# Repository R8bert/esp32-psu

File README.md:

# ⚡ ESP32-Controlled Lab Power Supply

A smart, programmable **lab power supply** controlled by an **ESP32 microcontroller**.  
This project combines hardware design and firmware development to provide precise, remote control over voltage and current using a **custom-designed PCB**.

---

## 🧠 Project Overview

This project was created to make a standard lab power supply smarter and easier to use.  
By adding an ESP32 and a custom interface board, I was able to control voltage, current, and safety features remotely — either through a web dashboard, serial commands, or a mobile app.

The repository includes both the **ESP32 firmware** and **PCB schematics** for full reproducibility.

---

## ⚙️ Features

- **Precise Voltage and Current Control**  
  Adjust and monitor power output in real time with fine-grained accuracy.

- **Multiple Control Interfaces**  
  Control the supply through a web interface, serial monitor, or a custom mobile app.

- **Programmable Output Profiles**  
  Automate experiments by predefining voltage/current sequences.

- **Built-in Safety Protections**  
  Includes software-based overvoltage and overcurrent protection to safeguard connected devices.

- **Custom PCB Design**  
  Handles signal conditioning and power control between the ESP32 and the lab power supply.

---

## 🧩 Components Used

| Component | Description |
|------------|-------------|
| **ESP32 DevKit** | Main controller, handles communication and web interface |
| **Custom PCB** | Connects ESP32 to lab supply, includes signal conditioning and protection |
| **Lab Power Supply** | Provides adjustable voltage and current output |
| **MOSFETs, Diodes, Resistors, Capacitors** | Used for power regulation and switching |
| **Connectors & Headers** | For input/output and debugging connections |

---

## 🔌 Schematics

The schematic below shows how the ESP32 interfaces with the lab power supply via the custom PCB.

---

## 💻 Firmware

The ESP32 firmware handles communication, user commands, and power control logic.

- Written in **C++** using the **Arduino framework**
- Communicates with the lab supply over digital I/O and serial protocols
- Supports **web-based control** via Wi-Fi and **serial communication**
- Implements **PID-style regulation** for smooth voltage and current control

### 🔧 Installation

1. Install the **Arduino IDE** or **PlatformIO** with ESP32 board support.  
2. Clone this repository.  
3. Open the firmware folder in your IDE.  
4. Compile and upload the code to the ESP32 board.  
5. Connect the ESP32 to the custom PCB and power supply.  

--
You can upload them directly to any PCB fabrication service (e.g., JLCPCB, PCBWay).

### 🔩 Assembly

Solder the through-hole and SMD components as labeled on the silkscreen.  
Pay attention to MOSFET orientation and connector alignment.

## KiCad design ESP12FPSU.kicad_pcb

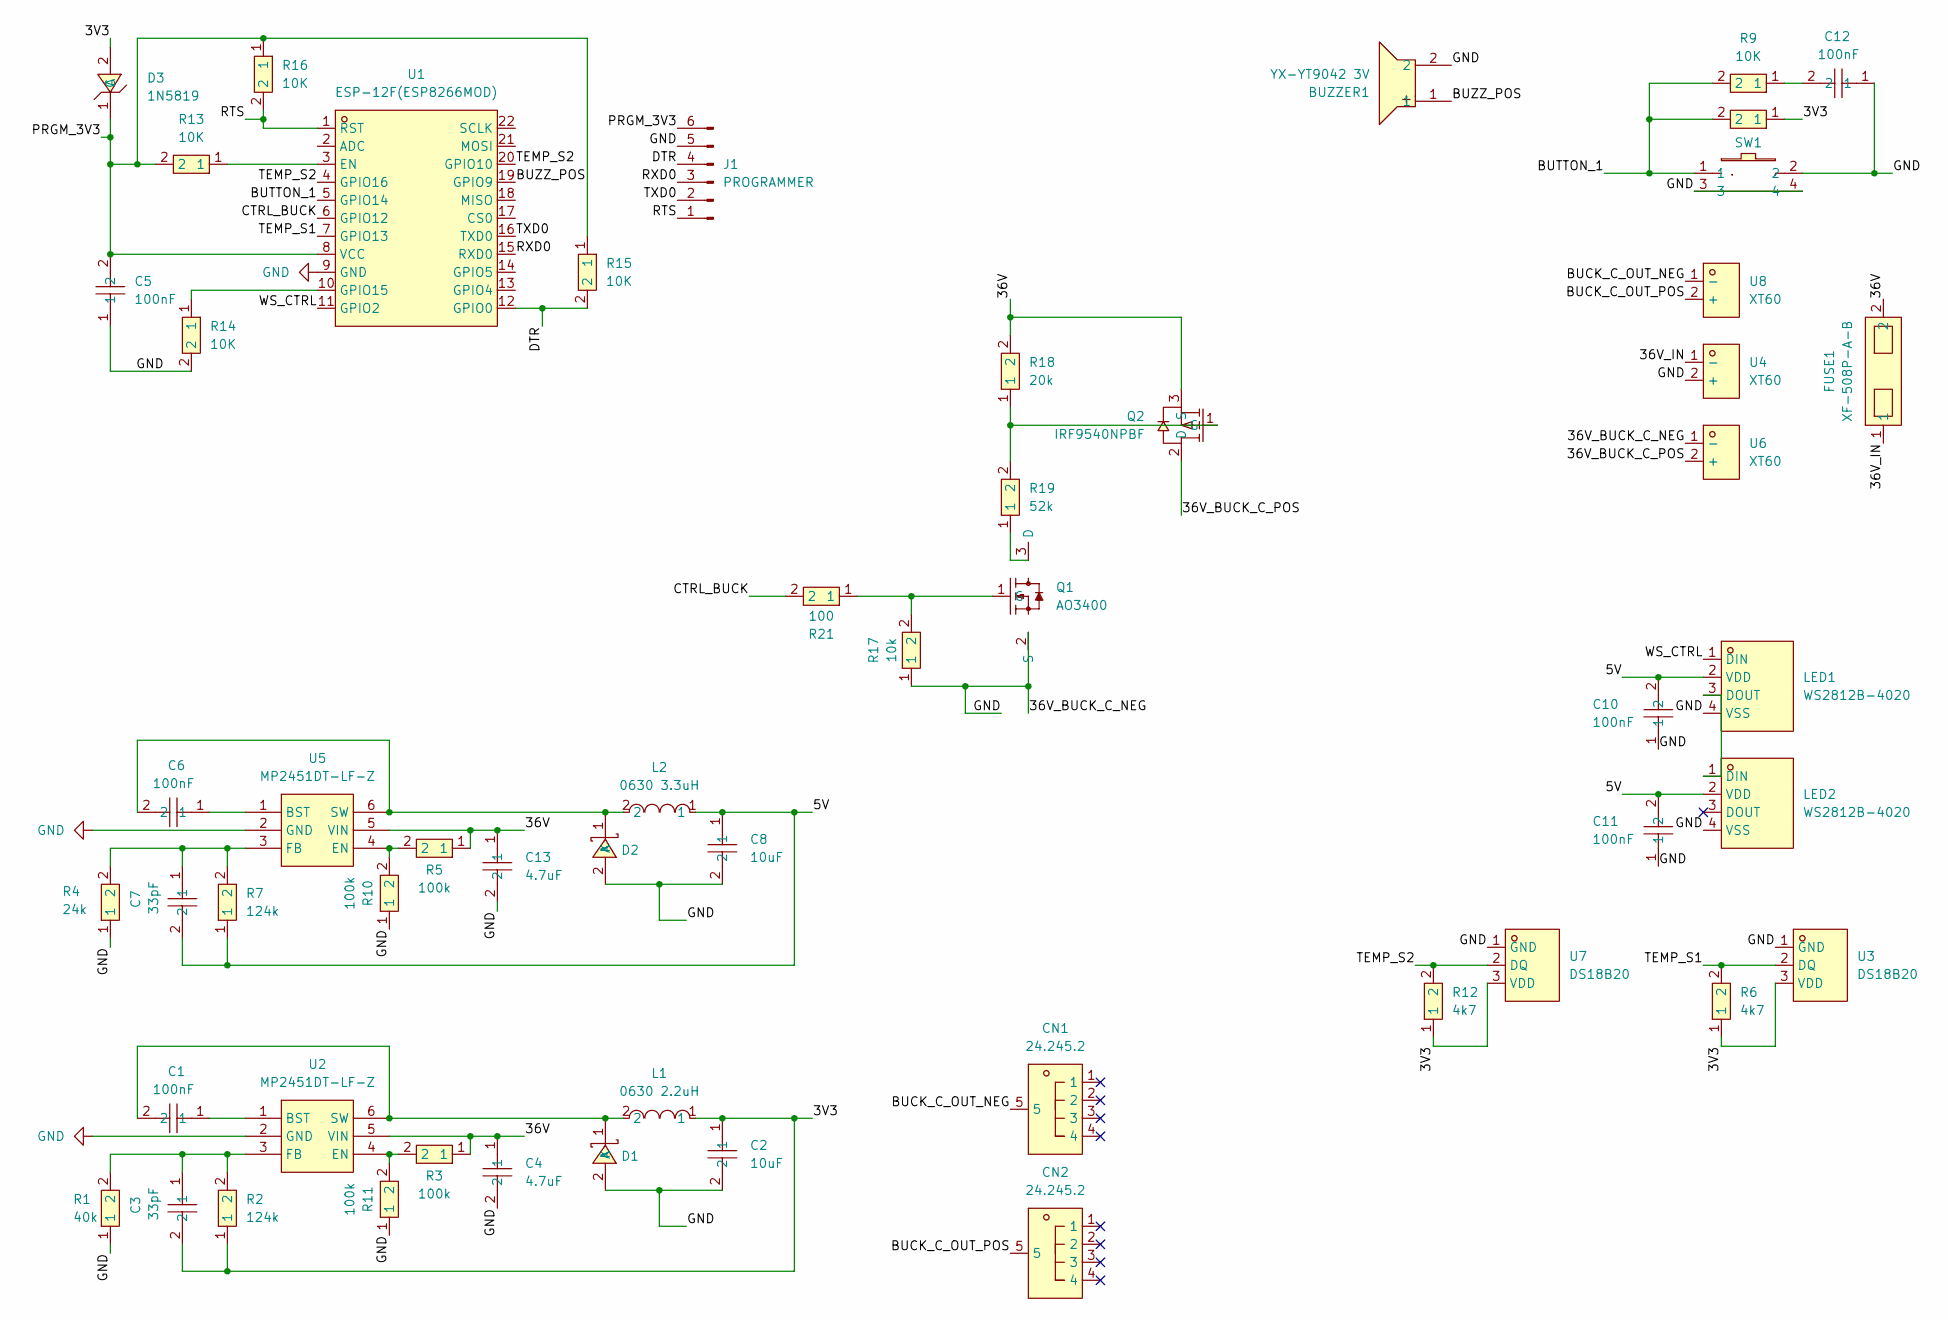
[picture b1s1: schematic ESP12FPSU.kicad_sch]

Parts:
BUZZER1: YX-YT9042 3V; BUZ-TH_BD9.0-P5.00-D0.6-FD; LCSC Part C781847
C1, C5, C6, C12: 100nF; C0603; LCSC Part C282519
C2, C8: 10uF; C1206; LCSC Part C105197
C3, C7: 33pF; C0603; LCSC Part C282519
C4, C13: 4.7uF; C1206; LCSC Part C105197
C10, C11: 100nF; C0603; LCSC Part C519946
CN1, CN2: 24.245.2; ANT-TH_L33.0-W12.0_BLACK; LCSC Part C7437327
D1, D2: SS24_C908678; SMA_L4.2-W2.7-LS5.1-RD; LCSC Part C908678
D3: 1N5819; SOD-123_L2.8-W1.8-LS3.7-RD; LCSC Part C402219
FUSE1: XF-508P-A-B; FUSE-TH_XF-508P-A-B; LCSC Part C19727304
J1: PROGRAMMER; PinHeader_1x06_P2.54mm_Vertical
L1: 0630 2.2uH; IND-SMD_L7.0-W6.6_0630CDMCCDS; LCSC Part C2961890
L2: 0630 3.3uH; IND-SMD_L7.0-W6.6_0630CDMCCDS; LCSC Part C2961890
LED1, LED2: WS2812B-4020; LED-SMD_WS2812B-4020; LCSC Part C965557
Q1: AO3400; SOT-23-3_L2.9-W1.3-P1.90-LS2.4-BR; LCSC Part C181090
Q2: IRF9540NPBF; TO-220-3_L10.0-W4.5-P2.54-L; LCSC Part C2575
R1: 40k; R0603; LCSC Part C2918515
R2, R7: 124k; R0603; LCSC Part C2918515
R3, R5, R10, R11: 100k; R0603; LCSC Part C2918515
R4: 24k; R0603; LCSC Part C2918515
R6, R12: 4k7; R0603; LCSC Part C2918515
R8, R9, R13, R14, R15, R16: 10K; R0603; LCSC Part C2918515
R17: 10k; R0603; LCSC Part C2918515
R18: 20k; R2512; LCSC Part C2889857
R19: 52k; R2512; LCSC Part C2889857
R21: 100; R0603; LCSC Part C2918515
SW1: Button-6x6x9-Right-Angle; SW-TH_BBJ; LCSC Part C71842
U1: ESP-12F(ESP8266MOD); WIFIM-SMD_ESP-12F-ESP8266MOD; LCSC Part C82891
U2, U5: MP2451DT-LF-Z; SOT-23-6_L2.9-W1.6-P0.95-LS2.8-BR; LCSC Part C14123
U3, U7: DS18B20; TO-92-3_L4.9-W3.7-P1.27-L; LCSC Part C376006
U4, U6, U8: XT60; CONN-TH_XT60; LCSC Part C98733

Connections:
/3V3: C2.1, C3.2, D3.2 (A), L1.1, R2.1, R6.1, R8.1, R12.1, U3.3 (VDD), U7.3 (VDD)
/5V: C7.2, C8.1, C10.2, C11.2, L2.1, LED1.2 (VDD), LED2.2 (VDD), R7.1
/36V: C4.1, C13.1, FUSE1.2, Q2.3 (S), R3.1, R5.1, R18.2, U2.5 (VIN), U5.5 (VIN)
/36V_BUCK_C_POS: Q2.2 (D), U6.2 (+)
/36V_IN: FUSE1.1, U4.1 (-)
/BUCK_C_OUT_NEG: CN1.5, U8.1 (-)
/BUCK_C_OUT_POS: CN2.5, U8.2 (+)
/BUTTON_1: R8.2, R9.2, SW1.1, U1.5 (GPIO14)
/BUZZ_POS: BUZZER1.1, U1.19 (GPIO9)
/CTRL_BUCK: R21.2, U1.6 (GPIO12)
/DTR: J1.4, R15.2, U1.12 (GPIO0)
/PRGM_3V3: C5.2, D3.1 (C), J1.6, R13.2, R15.1, R16.1, U1.8 (VCC)
/RTS: J1.1, R16.2, U1.1 (RST)
/RXD0: J1.3, U1.15 (RXD0)
/TEMP_S1: R6.2, U1.7 (GPIO13), U3.2 (DQ)
/TEMP_S2: R12.2, U1.4 (GPIO16), U1.20 (GPIO10), U7.2 (DQ)
/TXD0: J1.2, U1.16 (TXD0)
/WS_CTRL: LED1.1 (DIN), U1.11 (GPIO2)
GND: BUZZER1.2, C2.2, C4.2, C5.1, C8.2, C10.1, C11.1, C12.1, C13.2, D1.2 (A), D2.2 (A), J1.5, LED1.4 (VSS), LED2.4 (VSS), Q1.2 (S), R1.1, R4.1, R10.1, R11.1, R14.2, R17.1, SW1.2, SW1.3, SW1.4, U1.9 (GND), U2.2 (GND), U3.1 (GND), U4.2 (+), U5.2 (GND), U6.1 (-), U7.1 (GND)
unnamed: C12.2, R9.1
unnamed: C1.2, D1.1 (K), L1.2, U2.6 (SW)
unnamed: C6.2, D2.1 (K), L2.2, U5.6 (SW)
unnamed: LED1.3 (DOUT), LED2.1 (DIN)
unnamed: Q1.3 (D), R19.1
unnamed: Q1.1 (G), R17.2, R21.1
unnamed: Q2.1 (G), R18.1, R19.2
unnamed: R13.1, U1.3 (EN)
unnamed: R14.1, U1.10 (GPIO15)
unnamed: C1.1, U2.1 (BST)
unnamed: R3.2, R11.2, U2.4 (EN)
unnamed: C3.1, R1.2, R2.2, U2.3 (FB)
unnamed: C6.1, U5.1 (BST)
unnamed: R5.2, R10.2, U5.4 (EN)
unnamed: C7.1, R4.2, R7.2, U5.3 (FB)

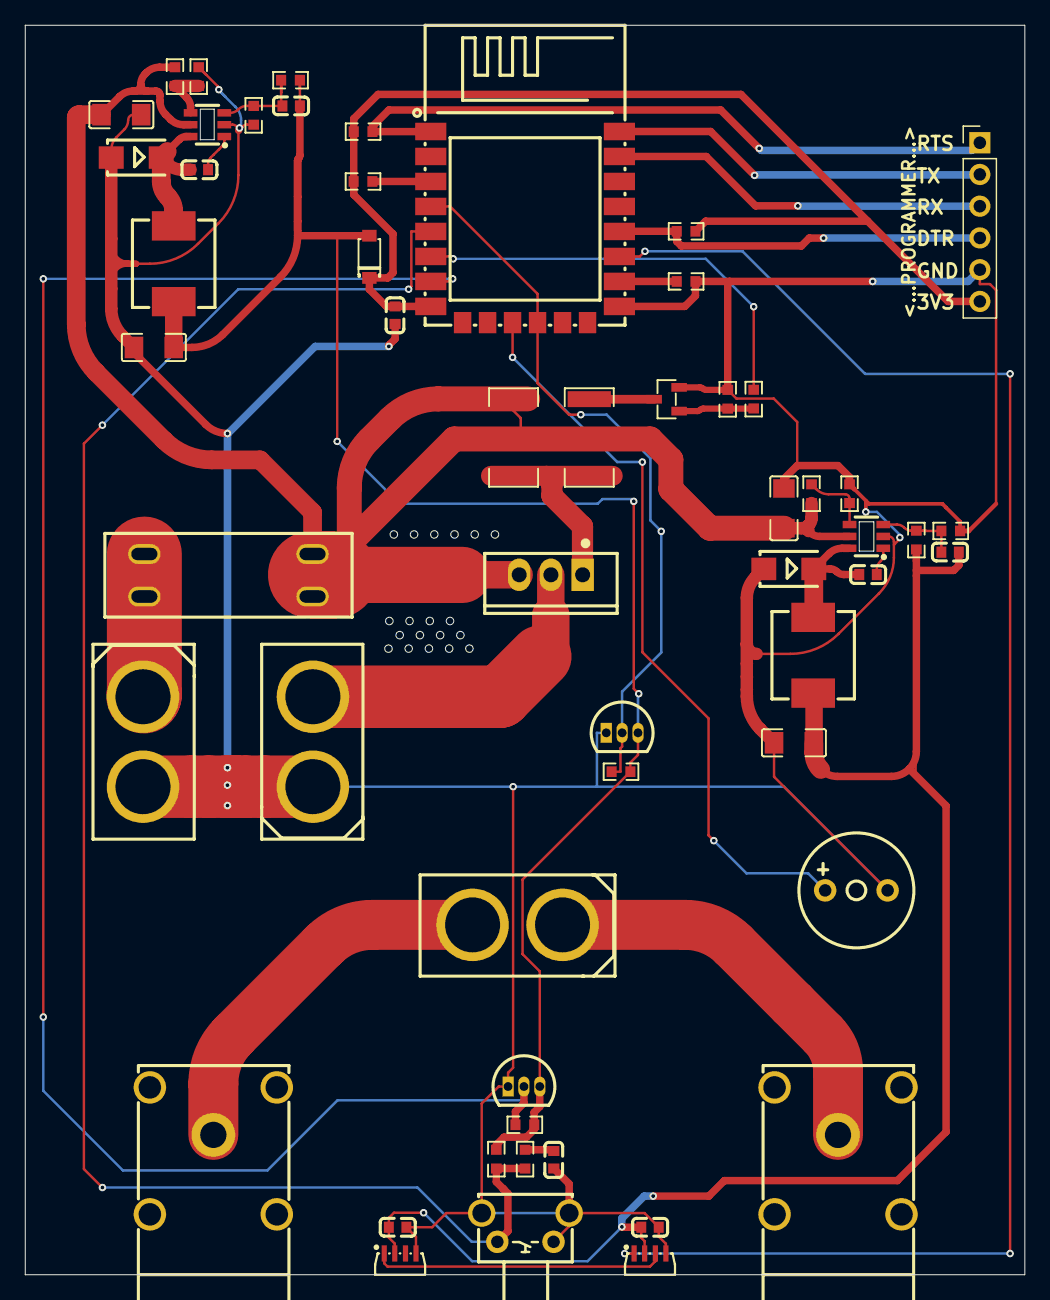
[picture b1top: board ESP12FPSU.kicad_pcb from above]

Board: 2 copper layers, 80.0 x 100.0 mm, 55 parts (0 on the bottom side), 34 nets.

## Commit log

2025-10-25 Revise README for clarity and detail
    Updated README to enhance project description and features.
